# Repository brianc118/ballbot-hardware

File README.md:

# Hardware for a self balancing ballbot

See eagle folder for PCB design files.
Requires Cadsoft Eagle 7.x and Autodesk Inventor 2015

Copyright (c) 2015 Brian Chen

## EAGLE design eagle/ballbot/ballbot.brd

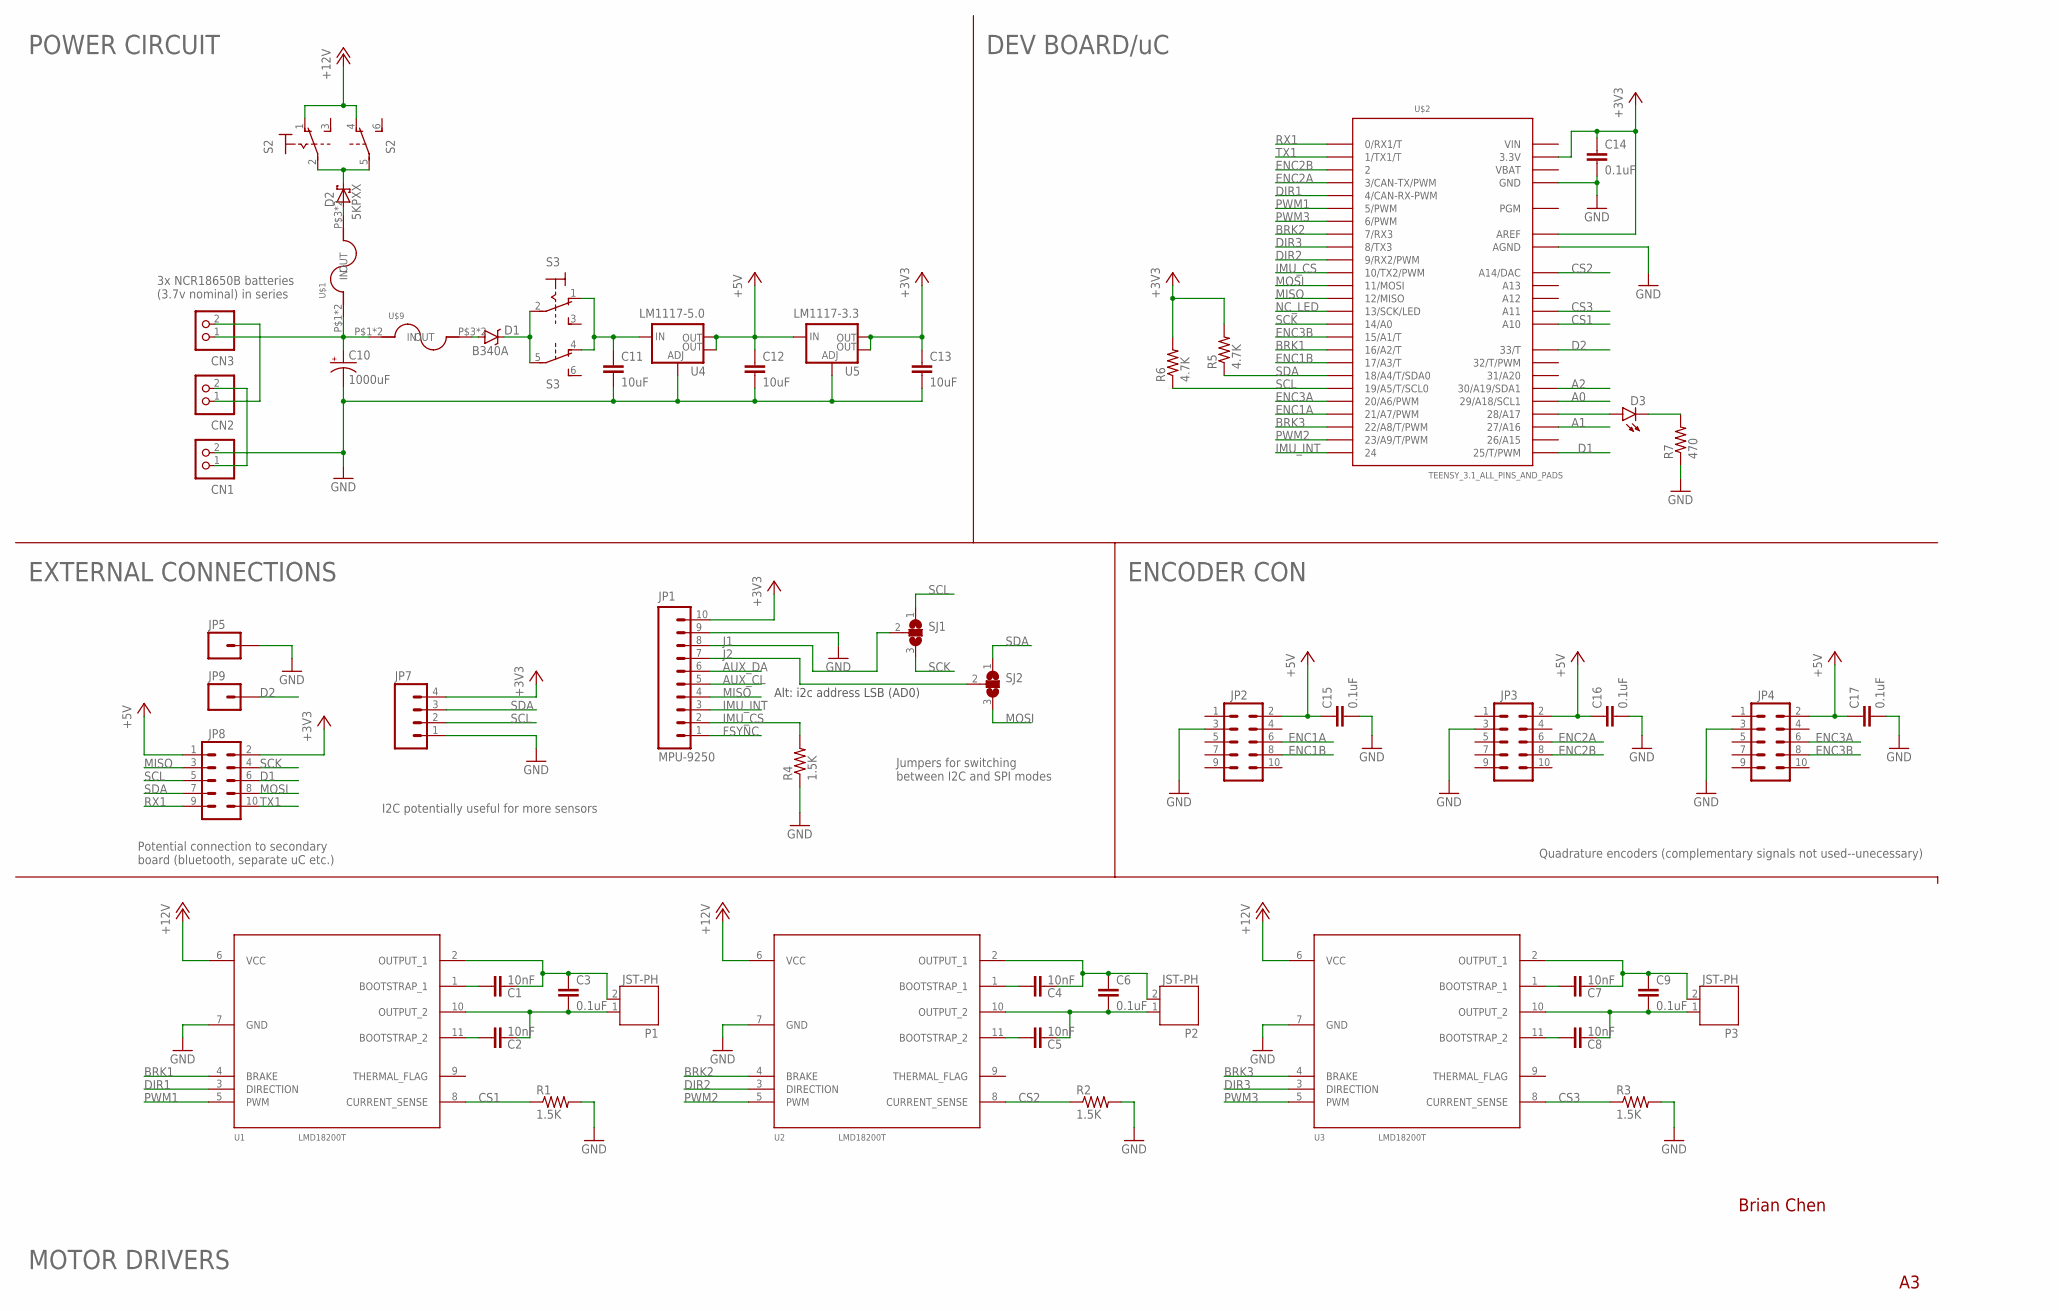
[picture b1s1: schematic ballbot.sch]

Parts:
C1, C2, C4, C5, C7, C8: 10nF; 0603-CAP
C3, C6, C9, C14, C15, C16, C17: 0.1uF; 0603-CAP
C10: 1000uF; CPOL-RADIAL-1000UF-25V
C11, C12, C13: 10uF; 0603-CAP
CN1, CN2, CN3: B2PS-VH
D1: B340A; SMA-DIODE
D2: 5KPXX; P6T15
D3: LED0603; LED-0603
JP1: MPU-9250; 1X10_NO_SILK
JP2, JP3, JP4: M05X2SHD; 2X5-SHROUDED
JP5, JP9: M01PTH_NO_SILK_YES_STOP; 1X01_NO_SILK
JP7: M04NO_SILK_ALL_ROUND; 1X04_NO_SILK_ALL_ROUND
JP8: M05X2NO_SILK; 2X5_NOSILK
P1, P2, P3: JST-PH; JST-PH2
R1, R2, R3, R4: 1.5K; 0603-RES
R5, R6: 4.7K; 0603-RES
R7: 470; 0603-RES
S2, S3: 320-938
SJ1, SJ2: SJ2W; SJ_2
U1, U2, U3: LMD18200T; TO-220-11
U4: LM1117-5.0; SOT223
U5: LM1117-3.3; SOT223
U$1, U$9: FUSE_HOLDER_; KEYSTONE_3568
U$2: TEENSY_3.1_ALL_PINS_AND_PADS; TEENSY3_ALL_PINS_&_PADS

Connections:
+3V3: C13.1, C14.1, JP1.10, JP7.4, JP8.2, R5.2, R6.2, U5.2 (OUT), U5.4 (OUT), U$2.3.3V, U$2.3.3V1 (3.3V), U$2.3.3V2 (3.3V), U$2.AREF
+5V: C12.1, C15.1, C16.1, C17.1, JP2.2, JP3.2, JP4.2, JP8.1, U4.2 (OUT), U4.4 (OUT), U5.3 (IN)
+12V: S2.1 (O), S2.4 (O), U1.6 (VCC), U2.6 (VCC), U3.6 (VCC)
A0: U$2.29 (29/A18/SCL1)
A1: U$2.27 (27/A16)
A2: U$2.30 (30/A19/SDA1)
AUX_CL: JP1.5
AUX_DA: JP1.6
BRK1: U1.4 (BRAKE), U$2.16/A2 (16/A2/T)
BRK2: U2.4 (BRAKE), U$2.7 (7/RX3)
BRK3: U3.4 (BRAKE), U$2.22/A8 (22/A8/T/PWM)
CS1: R1.1, U1.8 (CURRENT_SENSE), U$2.A10
CS2: R2.1, U2.8 (CURRENT_SENSE), U$2.RESET/DAC (A14/DAC)
CS3: R3.1, U3.8 (CURRENT_SENSE), U$2.A11
D1: JP8.6, U$2.25 (25/T/PWM)
D2: JP9.1, U$2.33 (33/T)
DIR1: U1.3 (DIRECTION), U$2.4 (4/CAN-RX-PWM)
DIR2: U2.3 (DIRECTION), U$2.9 (9/RX2/PWM)
DIR3: U3.3 (DIRECTION), U$2.8 (8/TX3)
ENC1A: JP2.6, U$2.21/A7 (21/A7/PWM)
ENC1B: JP2.8, U$2.17/A3 (17/A3/T)
ENC2A: JP3.6, U$2.3 (3/CAN-TX/PWM)
ENC2B: JP3.8, U$2.2
ENC3A: JP4.6, U$2.20/A6 (20/A6/PWM)
ENC3B: JP4.8, U$2.15/A1 (15/A1/T)
FSYNC: JP1.1
GND: C10.-, C11.2, C12.2, C13.2, C14.2, C15.2, C16.2, C17.2, CN1.2, JP1.9, JP2.3, JP3.3, JP4.3, JP5.1, JP7.1, R1.2, R2.2, R3.2, R4.1, R7.1, U1.7 (GND), U2.7 (GND), U3.7 (GND), U4.1 (ADJ), U5.1 (ADJ), U$2.AGND, U$2.GND, U$2.GND1 (GND), U$2.GND2 (GND)
IMU_CS: JP1.2, R4.2, U$2.10 (10/TX2/PWM)
IMU_INT: JP1.3, U$2.24
J1: JP1.8, SJ1.2
J2: JP1.7, SJ2.2
MISO: JP1.4, JP8.3, U$2.12 (12/MISO)
MOSI: JP8.8, SJ2.3, U$2.11 (11/MOSI)
unnamed: C1.1, U1.1 (BOOTSTRAP_1)
unnamed: C2.1, U1.11 (BOOTSTRAP_2)
unnamed: C4.1, U2.1 (BOOTSTRAP_1)
unnamed: C5.1, U2.11 (BOOTSTRAP_2)
unnamed: C7.1, U3.1 (BOOTSTRAP_1)
unnamed: CN1.1, CN2.2
unnamed: CN2.1, CN3.2
unnamed: C11.1, S3.1 (O), S3.4 (O), U4.3 (IN)
unnamed: D2.C, S2.2, S2.5
unnamed: D2.A, U$1.P$3 (OUT), U$1.P$4 (OUT)
unnamed: D1.A, U$9.P$3 (OUT), U$9.P$4 (OUT)
unnamed: D3.A, U$2.28 (28/A17)
unnamed: D1.C, S3.2, S3.5
unnamed: D3.C, R7.2
unnamed: C8.1, U3.11 (BOOTSTRAP_2)
NA: C10.+, CN3.1, U$1.P$1 (IN), U$1.P$2 (IN), U$9.P$1 (IN), U$9.P$2 (IN)
NC_LED: U$2.13 (13/SCK/LED)
OUT_A1: C1.2, C3.1, P1.2, U1.2 (OUTPUT_1)
OUT_A2: C4.2, C6.1, P2.2, U2.2 (OUTPUT_1)
OUT_A3: C7.2, C9.1, P3.2, U3.2 (OUTPUT_1)
OUT_B1: C2.2, C3.2, P1.1, U1.10 (OUTPUT_2)
OUT_B2: C5.2, C6.2, P2.1, U2.10 (OUTPUT_2)
OUT_B3: C8.2, C9.2, P3.1, U3.10 (OUTPUT_2)
PWM1: U1.5 (PWM), U$2.5 (5/PWM)
PWM2: U2.5 (PWM), U$2.23/A9 (23/A9/T/PWM)
PWM3: U3.5 (PWM), U$2.6 (6/PWM)
RX1: JP8.9, U$2.0 (0/RX1/T)
SCK: JP8.4, SJ1.3, U$2.14/A0
SCL: JP7.2, JP8.5, R6.1, SJ1.1, U$2.19/A5 (19/A5/T/SCL0)
SDA: JP7.3, JP8.7, R5.1, SJ2.1, U$2.18/A4 (18/A4/T/SDA0)
TX1: JP8.10, U$2.1 (1/TX1/T)
VBAT: U$2.VBAT
VIN: U$2.VIN

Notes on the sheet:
Alt: i2c address LSB (AD0)
POWER CIRCUIT
DEV BOARD/uC
EXTERNAL CONNECTIONS
ENCODER CON
MOTOR DRIVERS
Brian Chen
Jumpers for switching between I2C and SPI modes
I2C potentially useful for more sensors
Potential connection to secondary board (bluetooth, separate uC etc.)
Quadrature encoders (complementary signals not used--unecessary)
3x NCR18650B batteries (3.7v nominal) in series

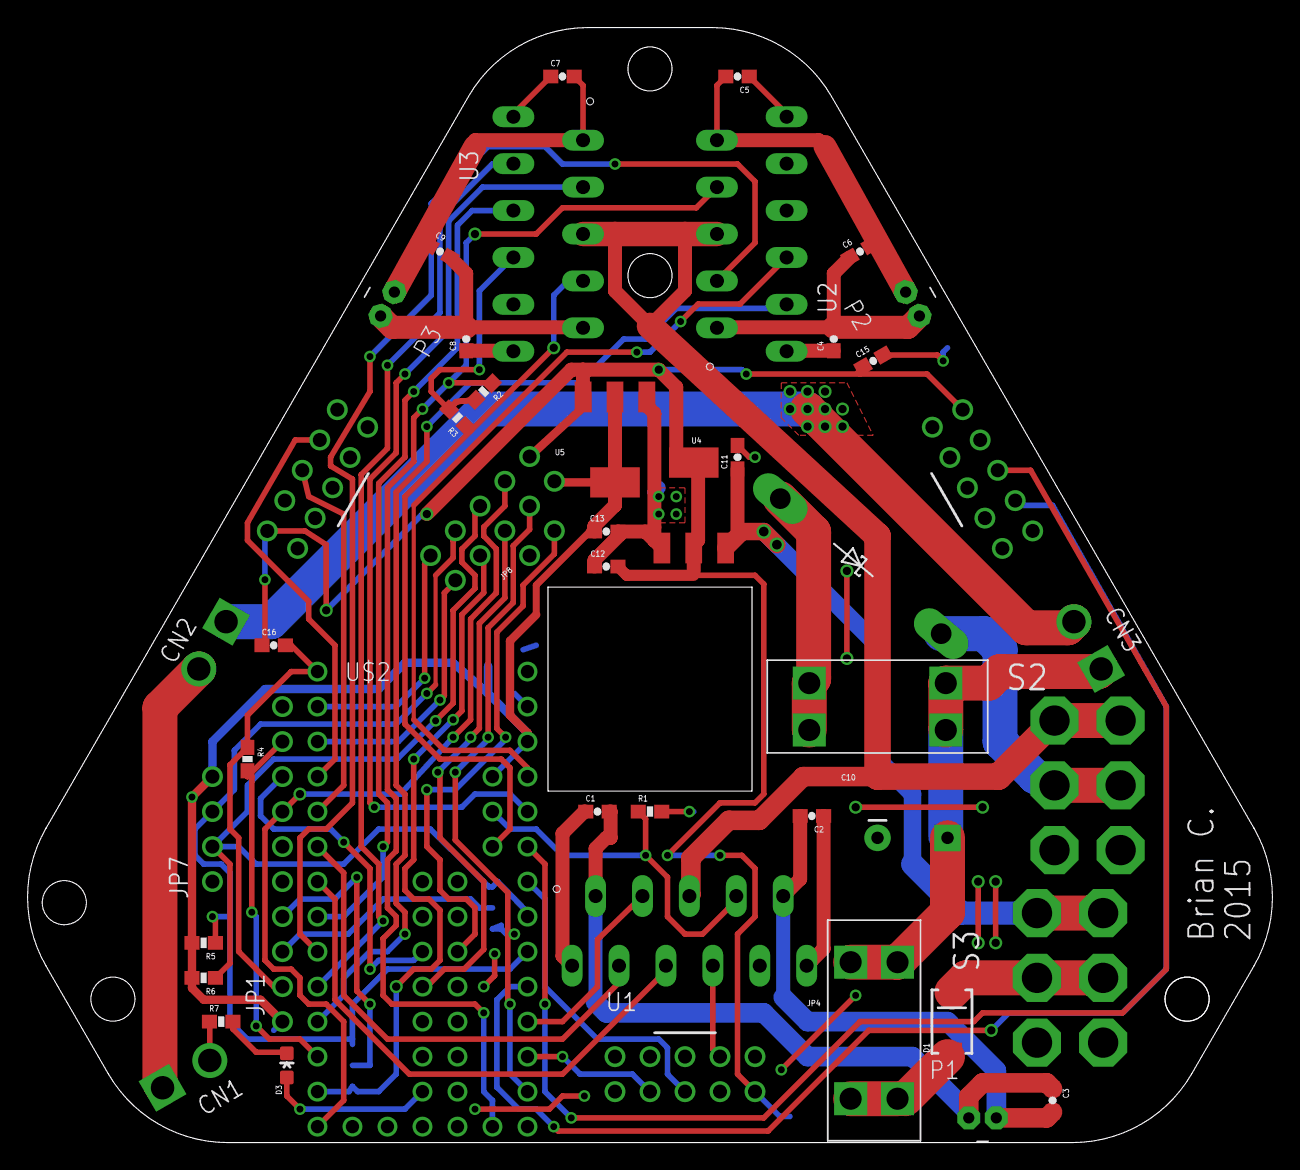
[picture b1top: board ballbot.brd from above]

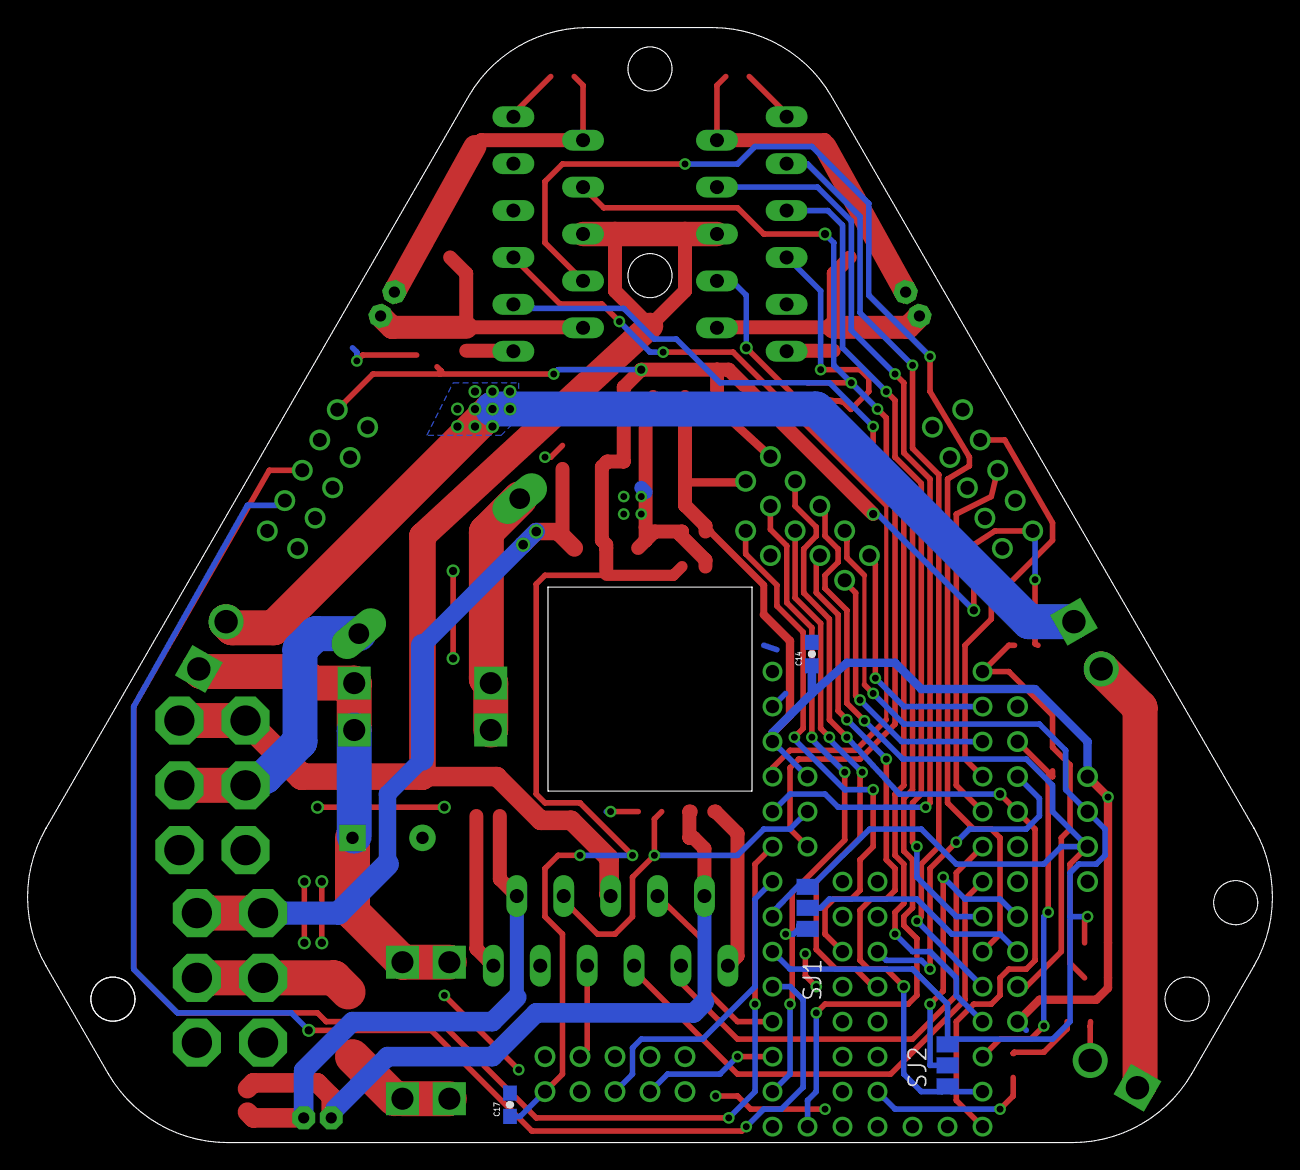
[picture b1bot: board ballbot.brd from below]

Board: 2 copper layers, 90.3 x 80.9 mm, 53 parts (4 on the bottom side), 57 nets.

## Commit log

2016-01-04 Added readme
2016-01-04 Fixed

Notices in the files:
parts and their libraries:
SparkFun-Capacitors: Licensing: Creative Commons ShareAlike 4.0 International - https://creativecommons.org/licenses/by-sa/4.0
